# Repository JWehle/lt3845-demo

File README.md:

# lt3845-demo
Demo board for the LT3845 buck converter controller.

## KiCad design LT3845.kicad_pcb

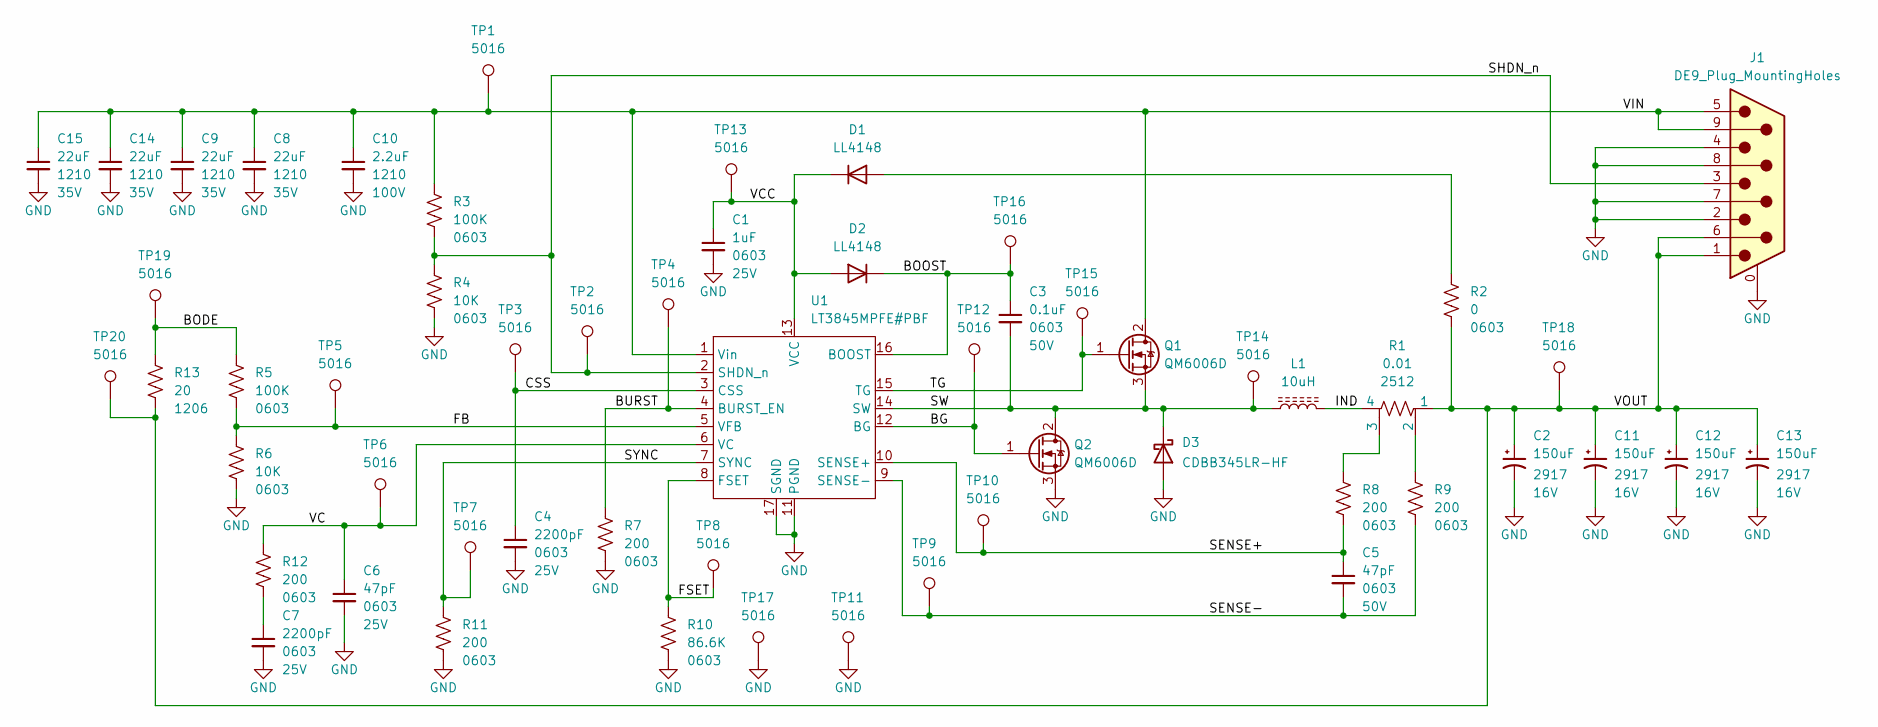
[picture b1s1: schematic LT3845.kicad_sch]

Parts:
C1: 1uF; C_0603_1608Metric_Pad1.08x0.95mm_HandSolder; Voltage 25V
C2, C11, C12, C13: 150uF; CP_EIA-7343-43_Kemet-X_Pad2.25x2.55mm_HandSolder; Voltage 16V
C3: 0.1uF; C_0603_1608Metric_Pad1.08x0.95mm_HandSolder; Voltage 50V
C4, C7: 2200pF; C_0603_1608Metric_Pad1.08x0.95mm_HandSolder; Voltage 25V
C5: 47pF; C_0603_1608Metric_Pad1.08x0.95mm_HandSolder; Voltage 50V
C6: 47pF; C_0603_1608Metric_Pad1.08x0.95mm_HandSolder; Voltage 25V
C8, C9, C14, C15: 22uF; C_1210_3225Metric_Pad1.33x2.70mm_HandSolder; Voltage 35V
C10: 2.2uF; C_1210_3225Metric_Pad1.33x2.70mm_HandSolder; Voltage 100V
D1, D2: LL4148; D_MiniMELF
D3: CDBB345LR-HF; D_SMB
J1: DE9_Plug_MountingHoles; DSUB-9_Male_Horizontal_P2.77x2.84mm_EdgePinOffset4.94mm_Hou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
L1: 10uH; L_Coilcraft_LPS4018
Q1, Q2: QM6006D; TO-252-2
R1: 0.01; R_Shunt_Vishay_WSK2512_6332Metric_T1.19mm
R2: 0; R_0603_1608Metric_Pad0.98x0.95mm_HandSolder
R3, R5: 100K; R_0603_1608Metric_Pad0.98x0.95mm_HandSolder
R4, R6: 10K; R_0603_1608Metric_Pad0.98x0.95mm_HandSolder
R7, R8, R9, R11, R12: 200; R_0603_1608Metric_Pad0.98x0.95mm_HandSolder
R10: 86.6K; R_0603_1608Metric_Pad0.98x0.95mm_HandSolder
R13: 20; R_1206_3216Metric_Pad1.30x1.75mm_HandSolder
TP1, TP2, TP3, TP4, TP5, TP6, TP7, TP8, TP9, TP10, TP11, TP12, TP13, TP14, TP15, TP16, TP17, TP18, TP19, TP20: 5016; TestPoint_Keystone_5016_Compact
U1: LT3845MPFE#PBF; HTSSOP-16-1EP_4.4x5mm_P0.65mm_EP3.4x5mm_Mask2.46x2.31mm_The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

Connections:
/BG: Q2.1 (G), TP12.1, U1.12 (BG)
/BODE: R5.1, R13.1, TP19.1
/BOOST: C3.1, D2.1 (K), TP16.1, U1.16 (BOOST)
/BURST: R7.1, TP4.1, U1.4 (BURST_EN)
/CSS: C4.1, TP3.1, U1.3 (CSS)
/FB: R5.2, R6.1, TP5.1, U1.5 (VFB)
/FSET: R10.1, TP8.1, U1.8 (FSET)
/IND: L1.2, R1.4
/SENSE+: C5.1, R8.2, TP10.1, U1.10 (SENSE+)
/SENSE-: C5.2, R9.2, TP9.1, U1.9 (SENSE-)
/SHDN_n: J1.3, R3.2, R4.1, TP2.1, U1.2 (SHDN_n)
/SW: C3.2, D3.1 (K), L1.1, Q1.3 (S), Q2.2 (D), TP14.1, U1.14 (SW)
/SYNC: R11.1, TP7.1, U1.7 (SYNC)
/TG: Q1.1 (G), TP15.1, U1.15 (TG)
/VC: C6.1, R12.1, TP6.1, U1.6 (VC)
/VCC: C1.1, D1.1 (K), D2.2 (A), TP13.1, U1.13 (VCC)
/VIN: C8.1, C9.1, C10.1, C14.1, C15.1, J1.5, J1.9, Q1.2 (D), R3.1, TP1.1, U1.1 (Vin)
/VOUT: C2.1, C11.1, C12.1, C13.1, J1.1, J1.6, R1.1, R2.2, R13.2, TP18.1, TP20.1
GND: C1.2, C2.2, C4.2, C6.2, C7.2, C8.2, C9.2, C10.2, C11.2, C12.2, C13.2, C14.2, C15.2, D3.2 (A), J1.0 (PAD), J1.2, J1.4, J1.7, J1.8, Q2.3 (S), R4.2, R6.2, R7.2, R10.2, R11.2, TP11.1, TP17.1, U1.11 (PGND), U1.17 (SGND)
unnamed: C7.1, R12.2
unnamed: D1.2 (A), R2.1
unnamed: R1.2, R9.1
unnamed: R1.3, R8.1

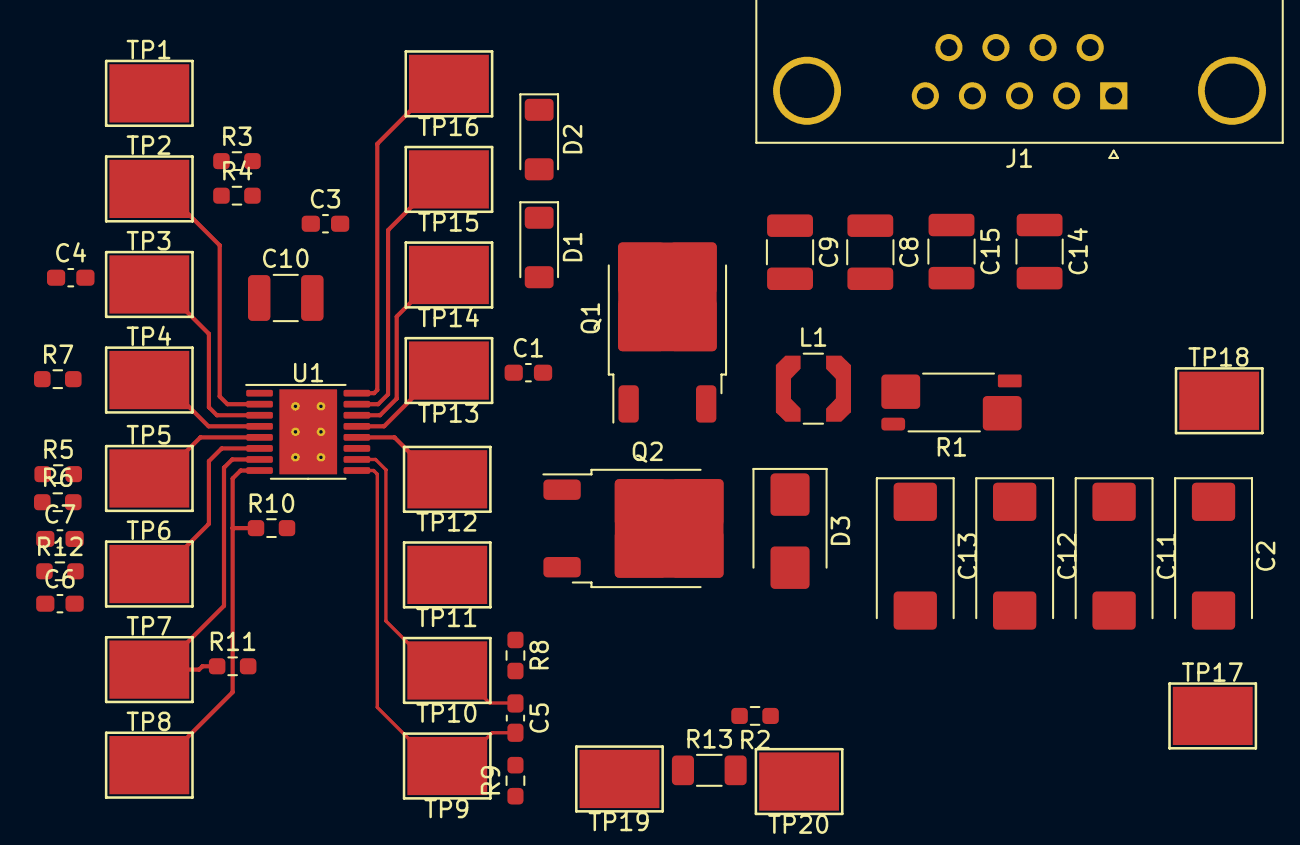
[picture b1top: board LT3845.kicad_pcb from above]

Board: 2 copper layers, 56 parts (0 on the bottom side), 23 nets.
